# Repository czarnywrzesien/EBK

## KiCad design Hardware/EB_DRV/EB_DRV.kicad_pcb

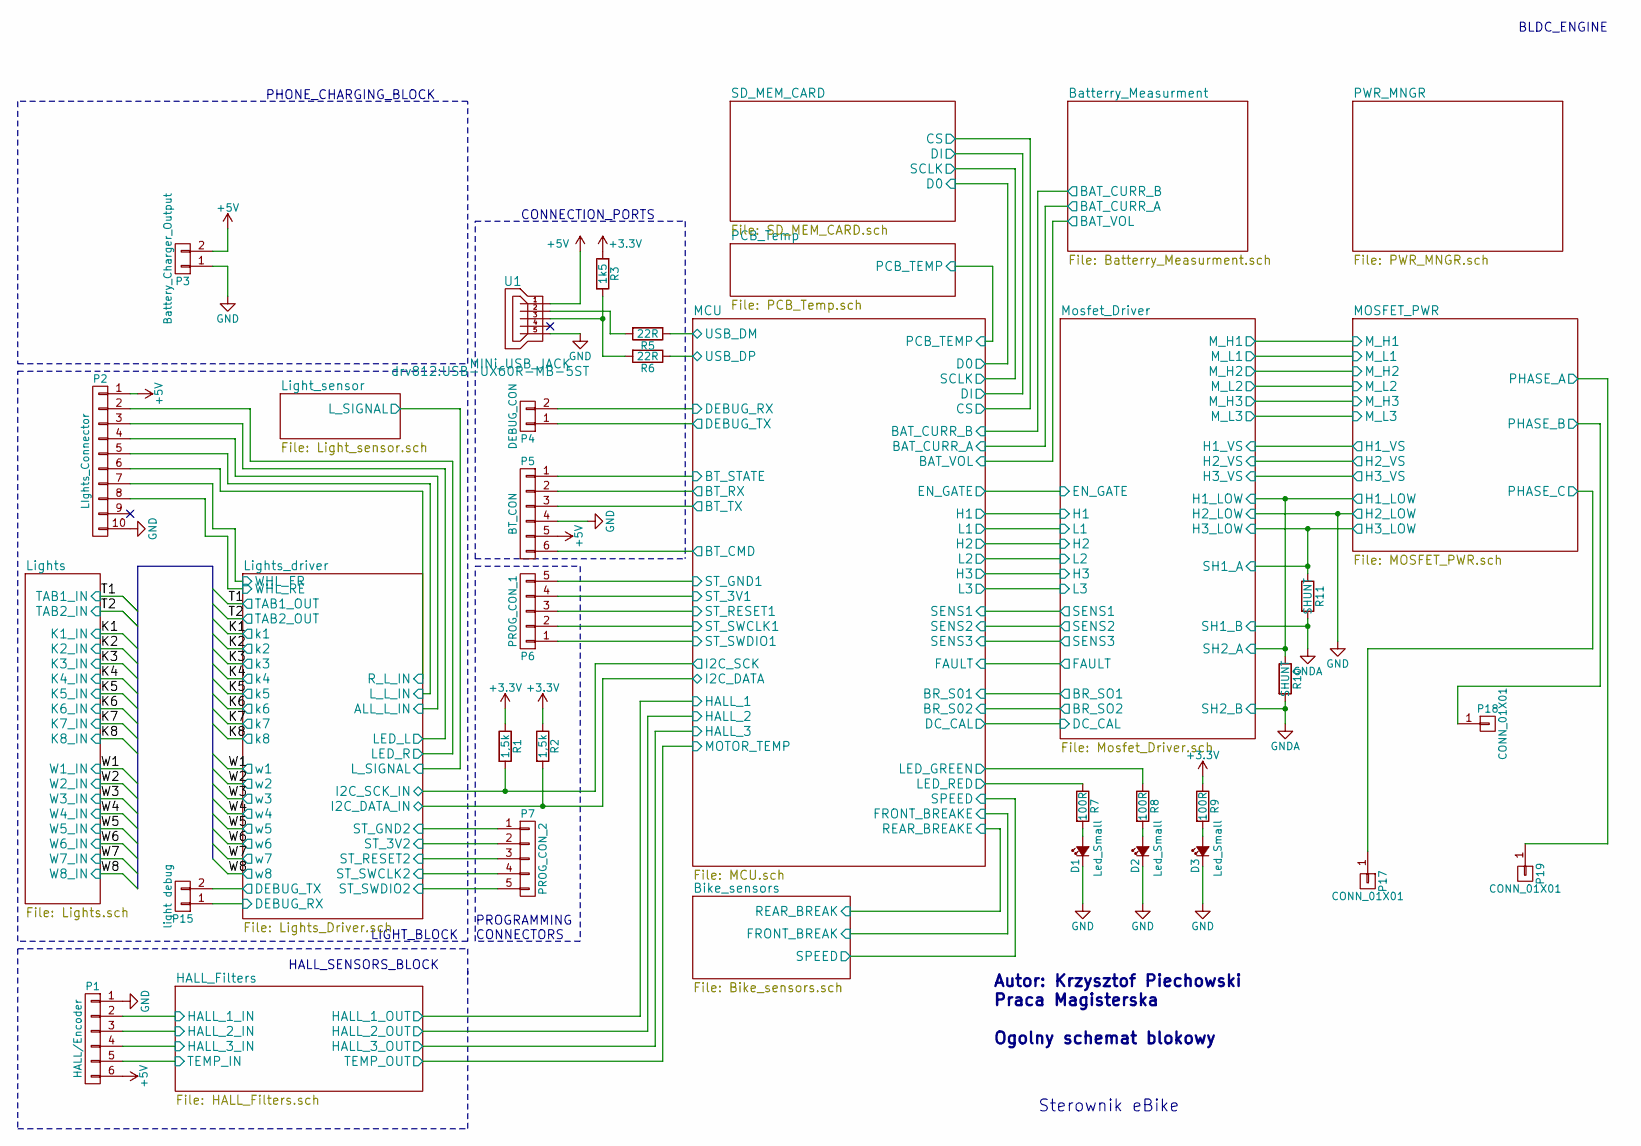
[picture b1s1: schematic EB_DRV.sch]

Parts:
D1, D2, D3: Led_Small; LED_0805
P1: HALL/Encoder; Pin_Header_Straight_1x06
P2: LIghts_Connector; Pin_Header_Straight_1x10
P3: Battery_Charger_Output; Pin_Header_Straight_1x02
P4: DEBUG_CON; Pin_Header_Straight_1x02
P5: BT_CON; Pin_Header_Straight_1x06
P6: PROG_CON_1; Pin_Header_Straight_1x05
P7: PROG_CON_2; Pin_Header_Straight_1x05
P15: light debug; Pin_Header_Straight_1x02
P17, P18, P19: CONN_01X01; SolderWirePad_single_2-5mmDrill
R1, R2: 1,5k; R_0805_HandSoldering
R3: 1k5; R_0805_HandSoldering
R5, R6: 22R; R_0805_HandSoldering
R7, R8, R9: 100R; R_0805_HandSoldering
R10, R11: SHUNT; R_0805_HandSoldering
U1: MINi_USB_JACK; USB-UX60R-MB-5ST

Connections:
+5V: P1.6, P2.1, P3.2, P5.5, U1.1; also elsewhere on the board
/HALL_Filters/HALL_1_IN: P1.2; also elsewhere on the board
/HALL_Filters/HALL_2_IN: P1.3; also elsewhere on the board
/HALL_Filters/HALL_3_IN: P1.4; also elsewhere on the board
/Lights_driver/ALL_L_IN: P2.4; also elsewhere on the board
/Lights_driver/DEBUG_RX: P15.1; also elsewhere on the board
/Lights_driver/DEBUG_TX: P15.2; also elsewhere on the board
/Lights_driver/LED_L: P2.3; also elsewhere on the board
/Lights_driver/LED_R: P2.2; also elsewhere on the board
/Lights_driver/L_L_IN: P2.5; also elsewhere on the board
/Lights_driver/R_L_IN: P2.6; also elsewhere on the board
/Lights_driver/ST_RESET2: P7.3; also elsewhere on the board
/Lights_driver/ST_SWCLK2: P7.4; also elsewhere on the board
/Lights_driver/ST_SWDIO2: P7.5; also elsewhere on the board
/Lights_driver/WHL_FR: P2.7; also elsewhere on the board
/Lights_driver/WHL_RE: P2.8; also elsewhere on the board
/MCU/BT_CMD: P5.6; also elsewhere on the board
/MCU/BT_RX: P5.2; also elsewhere on the board
/MCU/BT_STATE: P5.1; also elsewhere on the board
/MCU/BT_TX: P5.3; also elsewhere on the board
/MCU/DEBUG_RX: P4.2; also elsewhere on the board
/MCU/DEBUG_TX: P4.1; also elsewhere on the board
/MCU/I2C_DATA: R2.2; also elsewhere on the board
/MCU/I2C_SCK: R1.2; also elsewhere on the board
/MCU/LED_GREEN: R8.1; also elsewhere on the board
/MCU/LED_RED: R7.1; also elsewhere on the board
/MCU/MOTOR_TEMP: P1.5; also elsewhere on the board
/MCU/ST_RESET1: P6.3; also elsewhere on the board
/MCU/ST_SWCLK1: P6.2; also elsewhere on the board
/MCU/ST_SWDIO1: P6.1; also elsewhere on the board
/MCU/USB_DM: R5.1; also elsewhere on the board
/MCU/USB_DP: R6.1; also elsewhere on the board
/MOSFET_PWR/H1_LOW: R10.1; also elsewhere on the board
/MOSFET_PWR/H1_VS: P19.1; also elsewhere on the board
/MOSFET_PWR/H2_VS: P18.1; also elsewhere on the board
/MOSFET_PWR/H3_LOW: R11.1; also elsewhere on the board
/MOSFET_PWR/H3_VS: P17.1; also elsewhere on the board
GNDA: R10.2, R11.2; also elsewhere on the board
unnamed: D1.2 (A), R7.2
unnamed: D2.2 (A), R8.2
unnamed: D3.2 (A), R9.2
unnamed: R3.2, R6.2, U1.3
unnamed: R5.2, U1.2

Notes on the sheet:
LIGHT_BLOCK
PHONE_CHARGING_BLOCK
BLDC_ENGINE
HALL_SENSORS_BLOCK
PROGRAMMING CONNECTORS
CONNECTION_PORTS
Autor: Krzysztof Piechowski Praca Magisterska Ogolny schemat blokowy
Sterownik eBike

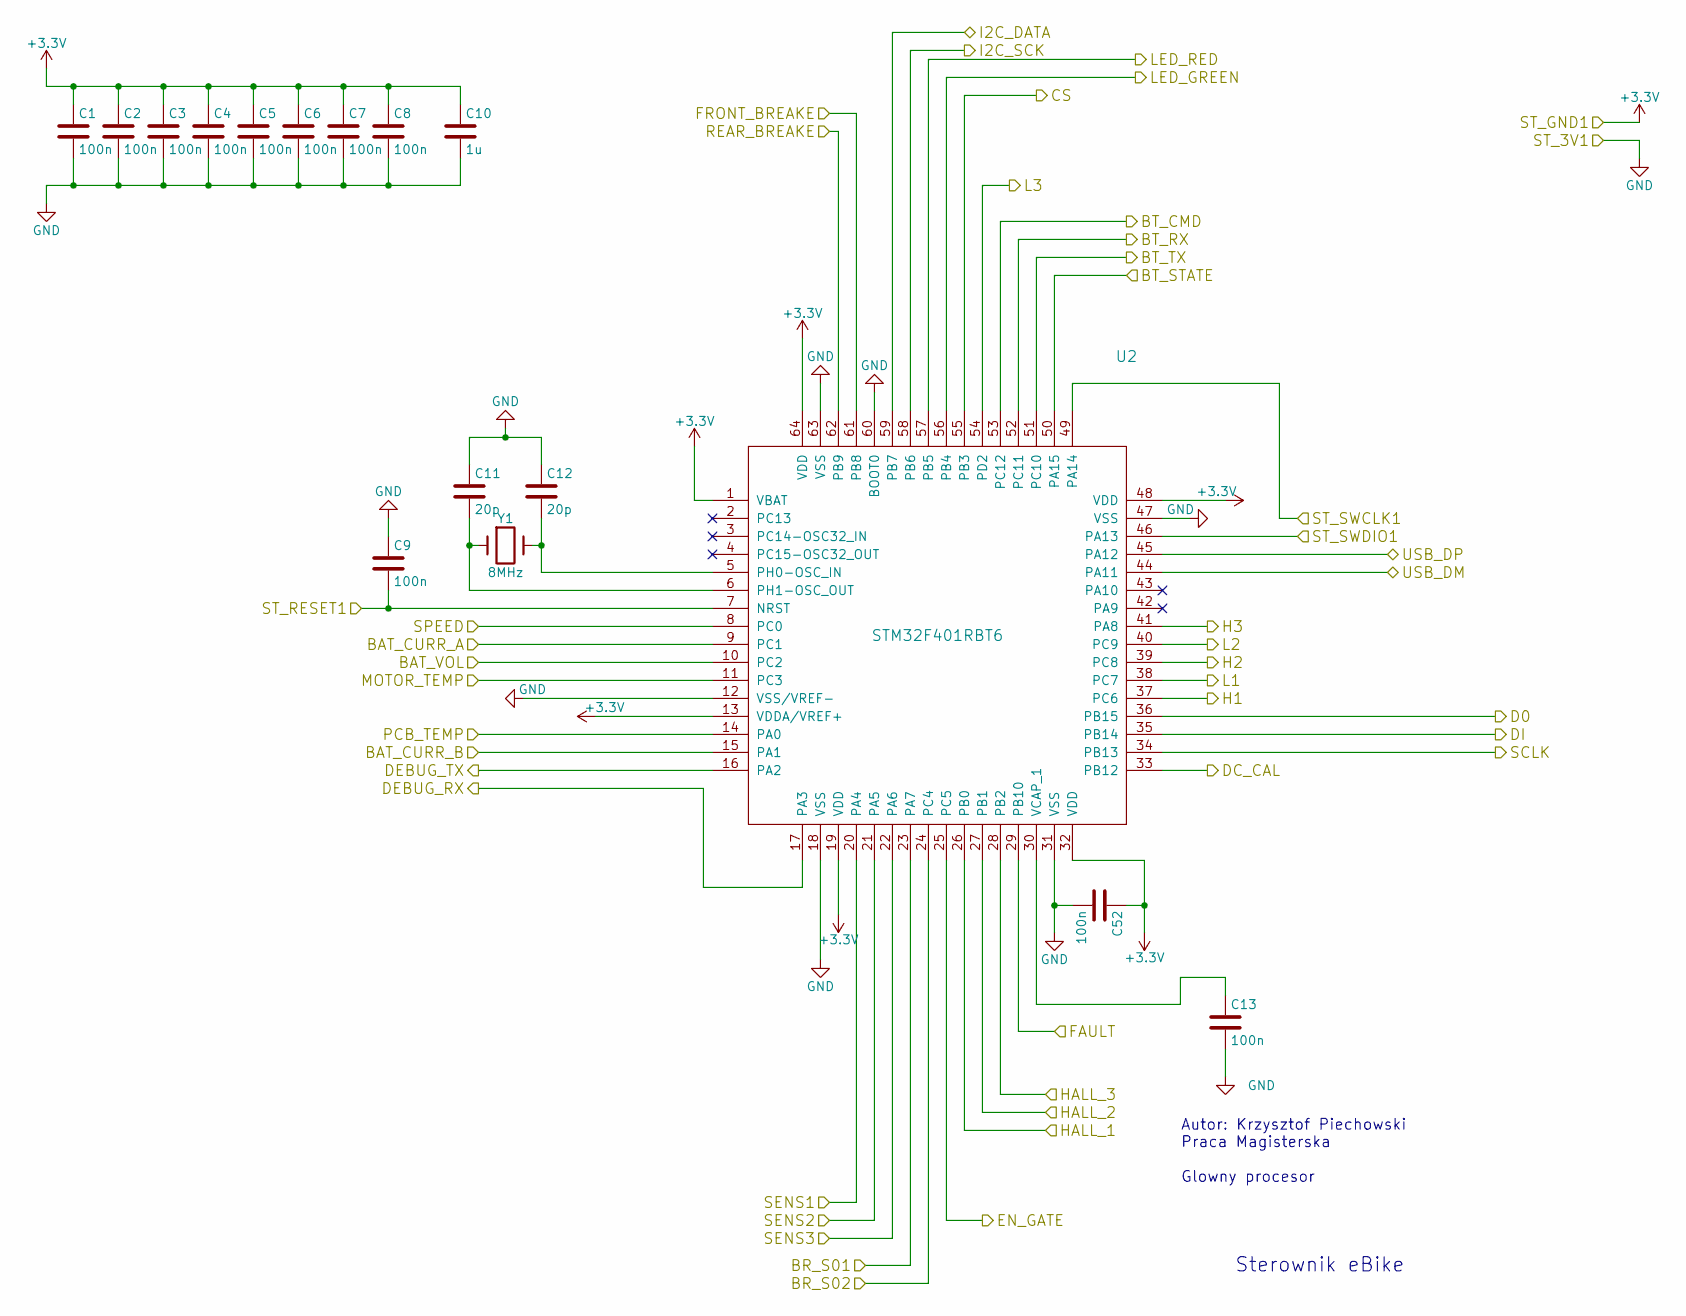
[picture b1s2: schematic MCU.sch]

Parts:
C1, C2, C3, C4, C5, C6, C7, C8, C9, C13, C52: 100n; C_0805_HandSoldering
C10: 1u; C_0805_HandSoldering
C11, C12: 20p; C_0805_HandSoldering
U2: STM32F401RBT6; LQFP-64_10x10mm_Pitch0.5mm
Y1: 8MHz; HC-18UV

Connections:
/Batterry_Measurment/BAT_CURR_A: U2.9 (PC1); also elsewhere on the board
/Batterry_Measurment/BAT_CURR_B: U2.15 (PA1); also elsewhere on the board
/Batterry_Measurment/BAT_VOL: U2.10 (PC2); also elsewhere on the board
/Bike_sensors/FRONT_BREAK: U2.61 (PB8); also elsewhere on the board
/Bike_sensors/REAR_BREAK: U2.62 (PB9); also elsewhere on the board
/Bike_sensors/SPEED: U2.8 (PC0); also elsewhere on the board
/MCU/BR_S01: U2.23 (PA7); also elsewhere on the board
/MCU/BR_S02: U2.24 (PC4); also elsewhere on the board
/MCU/BT_CMD: U2.53 (PC12); also elsewhere on the board
/MCU/BT_RX: U2.52 (PC11); also elsewhere on the board
/MCU/BT_STATE: U2.50 (PA15); also elsewhere on the board
/MCU/BT_TX: U2.51 (PC10); also elsewhere on the board
/MCU/CS: U2.55 (PB3)
/MCU/D0: U2.36 (PB15)
/MCU/DC_CAL: U2.33 (PB12); also elsewhere on the board
/MCU/DEBUG_RX: U2.17 (PA3); also elsewhere on the board
/MCU/DEBUG_TX: U2.16 (PA2); also elsewhere on the board
/MCU/DI: U2.35 (PB14)
/MCU/EN_GATE: U2.25 (PC5); also elsewhere on the board
/MCU/FAULT: U2.29 (PB10); also elsewhere on the board
/MCU/H1: U2.37 (PC6); also elsewhere on the board
/MCU/H2: U2.39 (PC8); also elsewhere on the board
/MCU/H3: U2.41 (PA8); also elsewhere on the board
/MCU/HALL_1: U2.26 (PB0); also elsewhere on the board
/MCU/HALL_2: U2.27 (PB1); also elsewhere on the board
/MCU/HALL_3: U2.28 (PB2); also elsewhere on the board
/MCU/I2C_DATA: U2.59 (PB7); also elsewhere on the board
/MCU/I2C_SCK: U2.58 (PB6); also elsewhere on the board
/MCU/L1: U2.38 (PC7); also elsewhere on the board
/MCU/L2: U2.40 (PC9); also elsewhere on the board
/MCU/L3: U2.54 (PD2); also elsewhere on the board
/MCU/LED_GREEN: U2.56 (PB4); also elsewhere on the board
/MCU/LED_RED: U2.57 (PB5); also elsewhere on the board
/MCU/MOTOR_TEMP: U2.11 (PC3); also elsewhere on the board
/MCU/PCB_TEMP: U2.14 (PA0); also elsewhere on the board
/MCU/SCLK: U2.34 (PB13)
/MCU/SENS1: U2.20 (PA4); also elsewhere on the board
/MCU/SENS2: U2.21 (PA5); also elsewhere on the board
/MCU/SENS3: U2.22 (PA6); also elsewhere on the board
/MCU/ST_RESET1: C9.2, U2.7 (NRST); also elsewhere on the board
/MCU/ST_SWCLK1: U2.49 (PA14); also elsewhere on the board
/MCU/ST_SWDIO1: U2.46 (PA13); also elsewhere on the board
/MCU/USB_DM: U2.44 (PA11); also elsewhere on the board
/MCU/USB_DP: U2.45 (PA12); also elsewhere on the board
unnamed: C11.2, U2.6 (PH1-OSC_OUT), Y1.1
unnamed: C12.2, U2.5 (PH0-OSC_IN), Y1.2
unnamed: C13.1, U2.30 (VCAP_1)

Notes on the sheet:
Autor: Krzysztof Piechowski Praca Magisterska Glowny procesor
Sterownik eBike

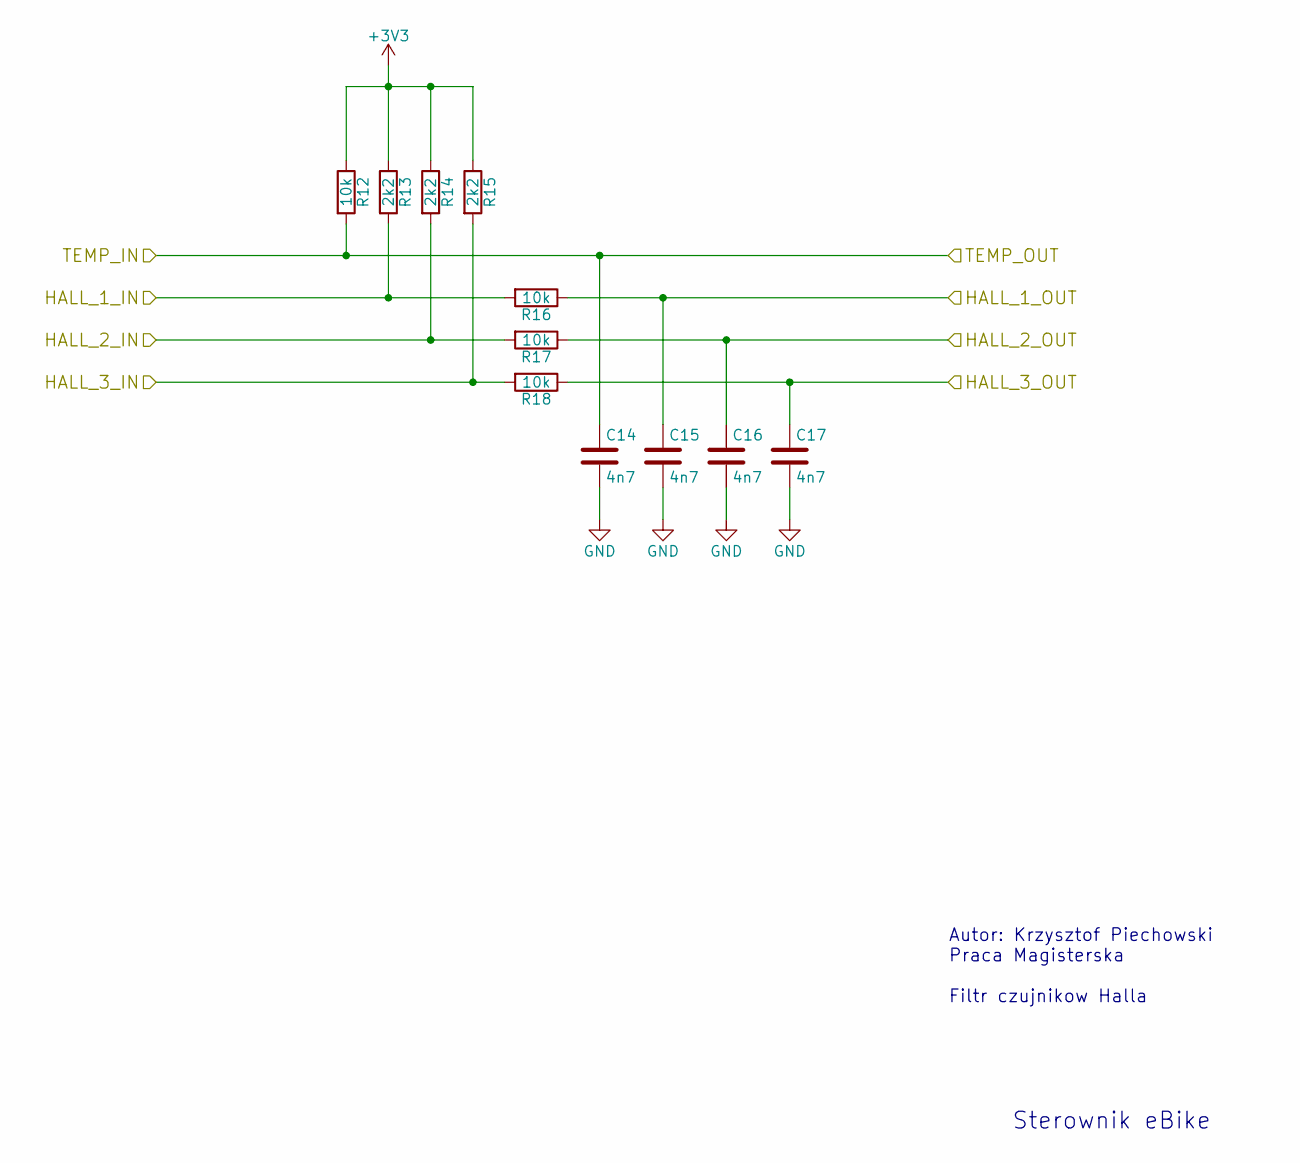
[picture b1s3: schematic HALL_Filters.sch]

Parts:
C14, C15, C16, C17: 4n7; C_0805_HandSoldering
R12, R16, R17, R18: 10k; R_0805_HandSoldering
R13, R14, R15: 2k2; R_0805_HandSoldering

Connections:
/HALL_Filters/HALL_1_IN: R13.2, R16.2; also elsewhere on the board
/HALL_Filters/HALL_2_IN: R14.2, R17.2; also elsewhere on the board
/HALL_Filters/HALL_3_IN: R15.2, R18.2; also elsewhere on the board
/MCU/HALL_1: C15.1, R16.1; also elsewhere on the board
/MCU/HALL_2: C16.1, R17.1; also elsewhere on the board
/MCU/HALL_3: C17.1, R18.1; also elsewhere on the board
/MCU/MOTOR_TEMP: C14.1, R12.2; also elsewhere on the board

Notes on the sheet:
Autor: Krzysztof Piechowski Praca Magisterska Filtr czujnikow Halla
Sterownik eBike

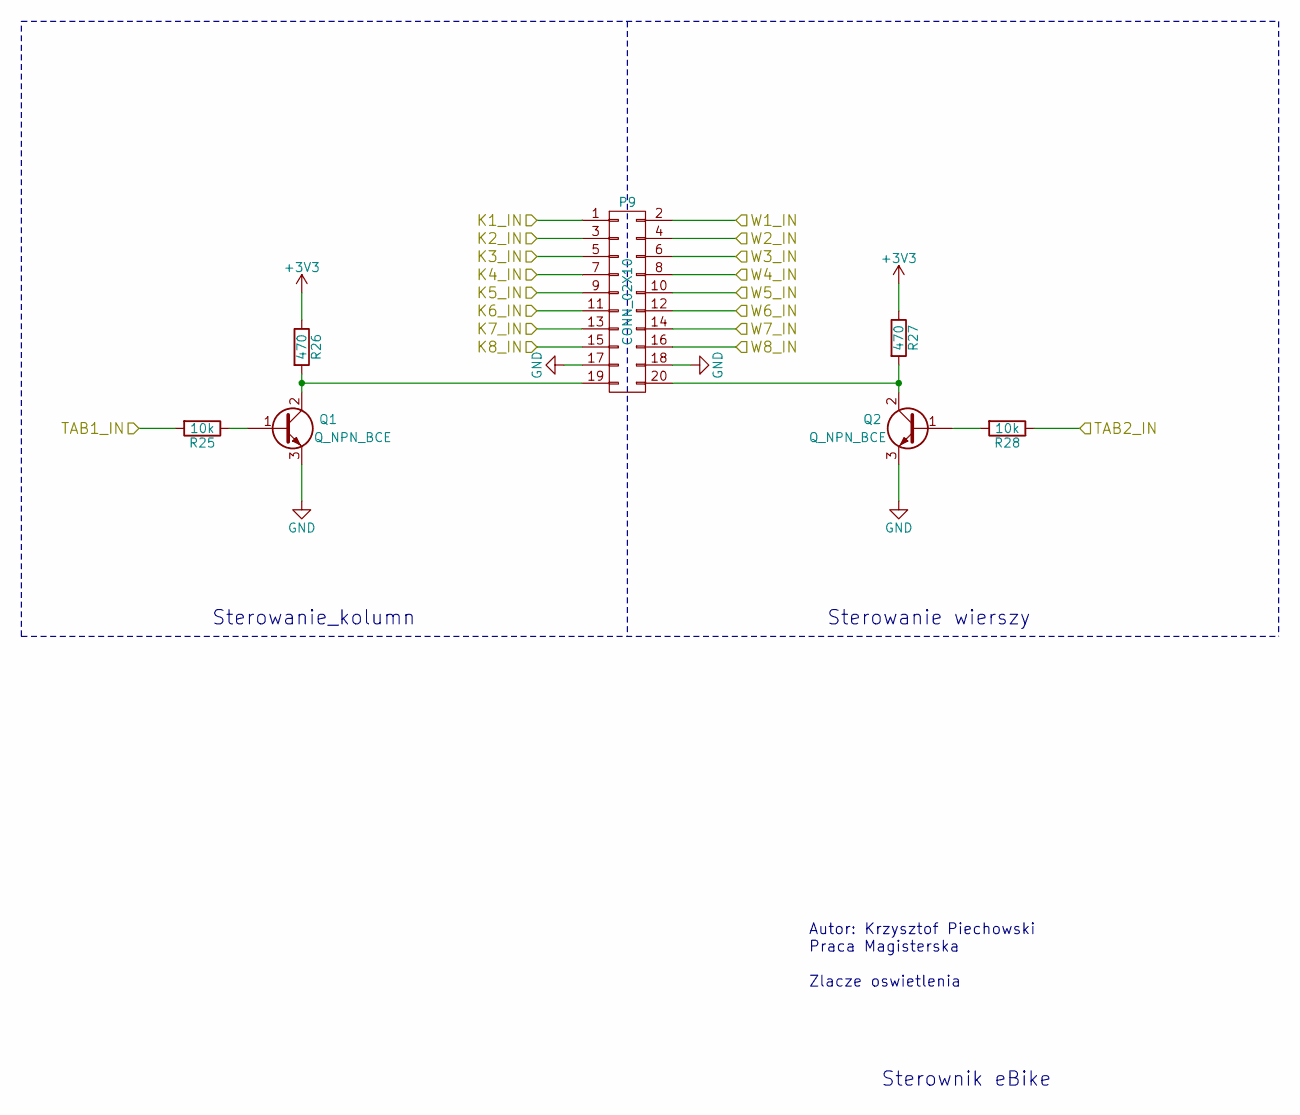
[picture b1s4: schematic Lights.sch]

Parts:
P9: CONN_02X10; Pin_Header_Straight_2x10
Q1, Q2: Q_NPN_BCE; SOT-323
R25, R28: 10k; R_0805_HandSoldering
R26, R27: 470; R_0805_HandSoldering

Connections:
/Lights/K1_IN: P9.1; also elsewhere on the board
/Lights/K2_IN: P9.3; also elsewhere on the board
/Lights/K3_IN: P9.5; also elsewhere on the board
/Lights/K4_IN: P9.7; also elsewhere on the board
/Lights/K5_IN: P9.9; also elsewhere on the board
/Lights/K6_IN: P9.11; also elsewhere on the board
/Lights/K7_IN: P9.13; also elsewhere on the board
/Lights/K8_IN: P9.15; also elsewhere on the board
/Lights/TAB1_IN: R25.2; also elsewhere on the board
/Lights/TAB2_IN: R28.1; also elsewhere on the board
/Lights/W1_IN: P9.2; also elsewhere on the board
/Lights/W2_IN: P9.4; also elsewhere on the board
/Lights/W3_IN: P9.6; also elsewhere on the board
/Lights/W4_IN: P9.8; also elsewhere on the board
/Lights/W5_IN: P9.10; also elsewhere on the board
/Lights/W6_IN: P9.12; also elsewhere on the board
/Lights/W7_IN: P9.14; also elsewhere on the board
/Lights/W8_IN: P9.16; also elsewhere on the board
unnamed: P9.19, Q1.2 (C), R26.2
unnamed: P9.20, Q2.2 (C), R27.2
unnamed: Q1.1 (B), R25.1
unnamed: Q2.1 (B), R28.2

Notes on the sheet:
Autor: Krzysztof Piechowski Praca Magisterska Zlacze oswietlenia
Sterowanie_kolumn
Sterowanie wierszy
Sterownik eBike

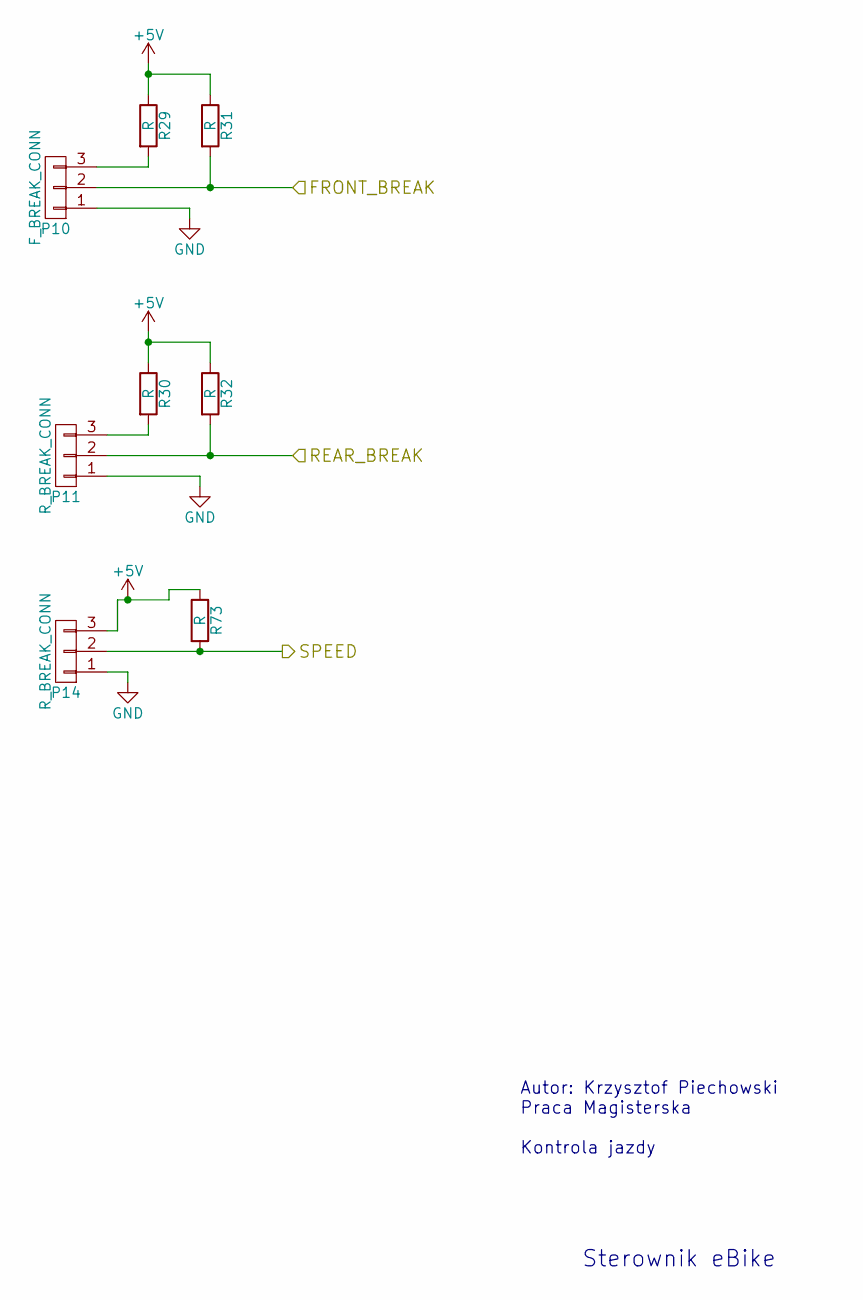
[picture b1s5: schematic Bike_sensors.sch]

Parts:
P10: F_BREAK_CONN; Pin_Header_Straight_1x03
P11, P14: R_BREAK_CONN; Pin_Header_Straight_1x03
R29, R30, R31, R32, R73: R; R_0805_HandSoldering

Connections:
+5V: P14.3, R29.1, R30.1, R31.1, R32.1, R73.1; also elsewhere on the board
/Bike_sensors/FRONT_BREAK: P10.2, R31.2; also elsewhere on the board
/Bike_sensors/REAR_BREAK: P11.2, R32.2; also elsewhere on the board
/Bike_sensors/SPEED: P14.2, R73.2; also elsewhere on the board
unnamed: P10.3, R29.2
unnamed: P11.3, R30.2

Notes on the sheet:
Autor: Krzysztof Piechowski Praca Magisterska Kontrola jazdy
Sterownik eBike

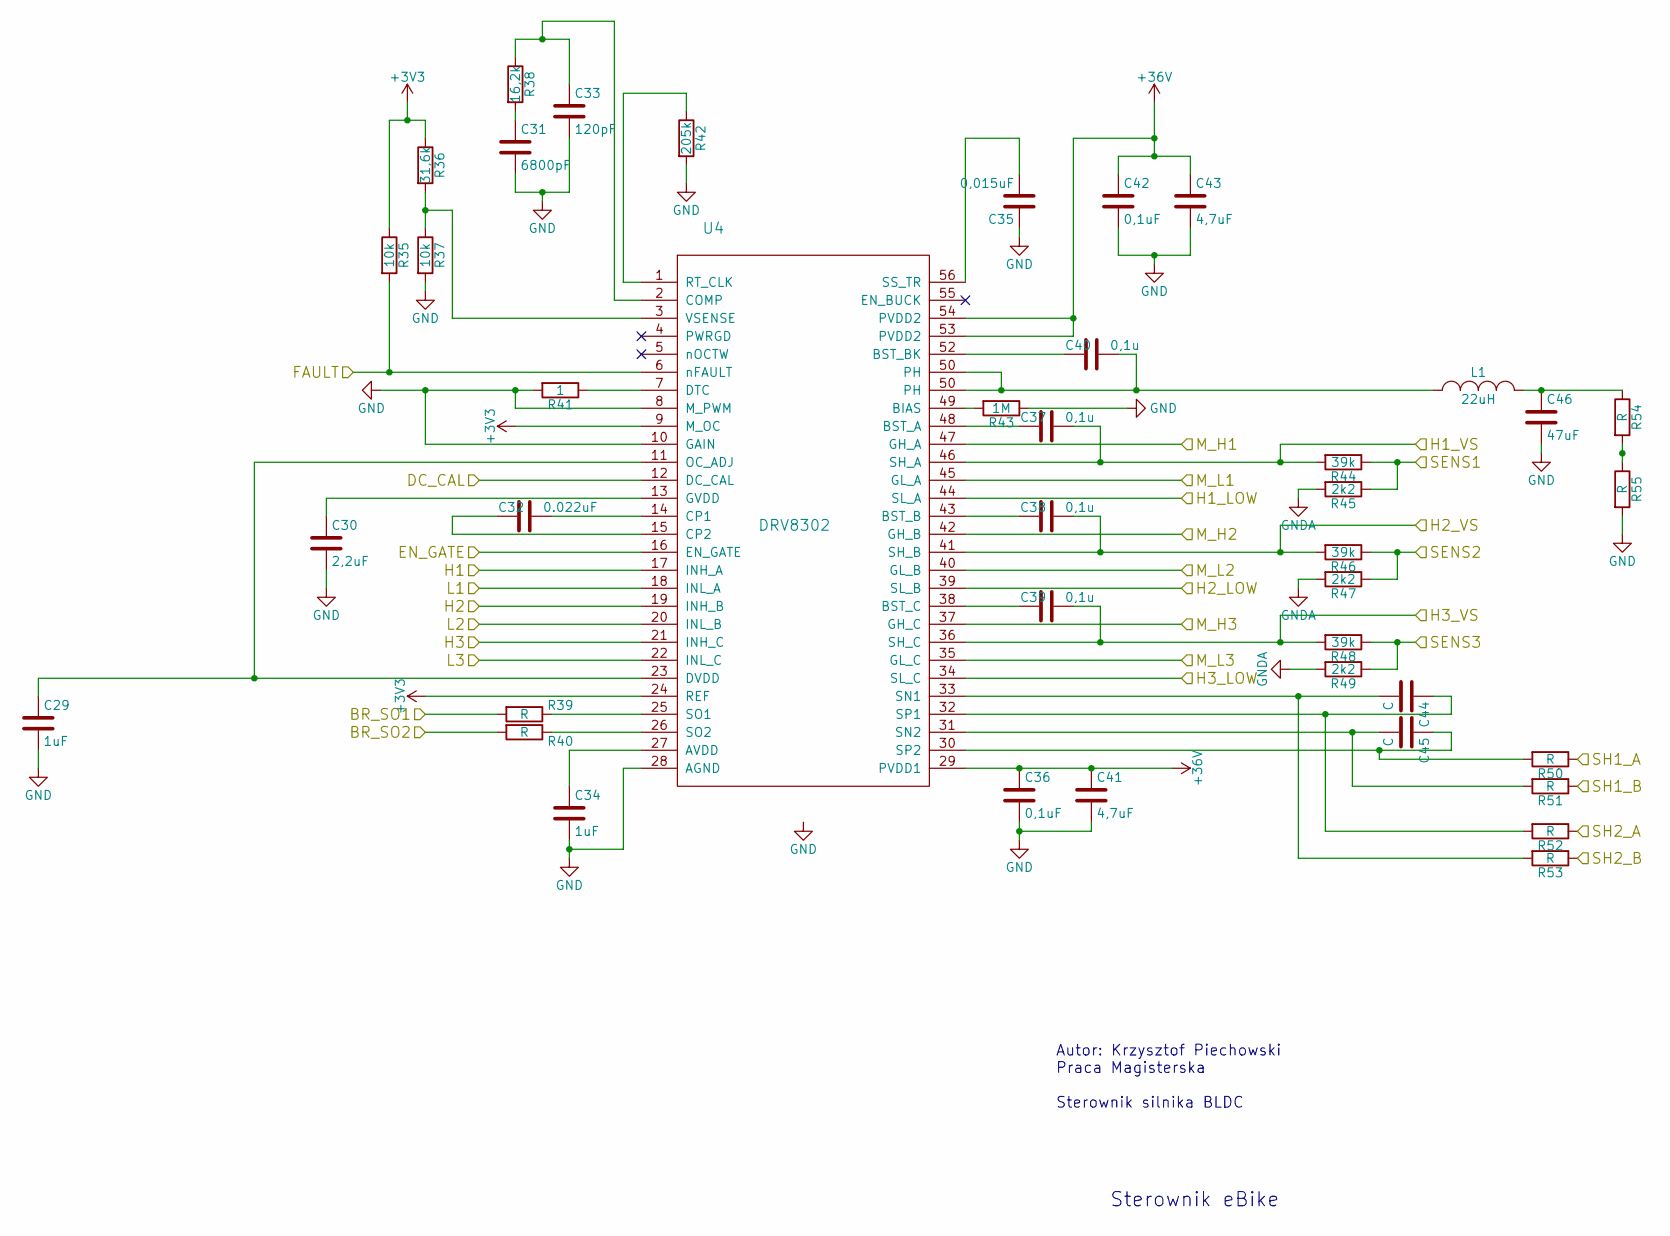
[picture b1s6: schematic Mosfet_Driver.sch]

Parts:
C29, C34: 1uF; C_0805_HandSoldering
C30: 2,2uF; C_0805_HandSoldering
C31: 6800pF; C_0805_HandSoldering
C32: 0.022uF; C_0805_HandSoldering
C33: 120pF; C_0805_HandSoldering
C35: 0,015uF; C_0805_HandSoldering
C36, C42: 0,1uF; C_0805_HandSoldering
C37, C38, C39, C40: 0,1u; C_0805_HandSoldering
C41, C43: 4,7uF; C_0805_HandSoldering
C44, C45: C; C_0805_HandSoldering
C46: 47uF; C_0805_HandSoldering
L1: 22uH; NR4018_HandSoldering
R35, R37: 10k; R_0805_HandSoldering
R36: 31,6k; R_0805_HandSoldering
R38: 16,2k; R_0805_HandSoldering
R39, R40, R50, R51, R52, R53, R54, R55: R; R_0805_HandSoldering
R41: 1; R_0805_HandSoldering
R42: 205k; R_0805_HandSoldering
R43: 1M; R_0805_HandSoldering
R44, R46, R48: 39k; R_0805_HandSoldering
R45, R47, R49: 2k2; R_0805_HandSoldering
U4: DRV8302; TSSOP-56-PP

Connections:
+36V: C36.1, C41.1, C42.1, C43.1, U4.29 (PVDD1), U4.53 (PVDD2), U4.54 (PVDD2); also elsewhere on the board
/MCU/BR_S01: R39.2; also elsewhere on the board
/MCU/BR_S02: R40.2; also elsewhere on the board
/MCU/DC_CAL: U4.12 (DC_CAL); also elsewhere on the board
/MCU/EN_GATE: U4.16 (EN_GATE); also elsewhere on the board
/MCU/FAULT: R35.2, U4.6 (nFAULT); also elsewhere on the board
/MCU/H1: U4.17 (INH_A); also elsewhere on the board
/MCU/H2: U4.19 (INH_B); also elsewhere on the board
/MCU/H3: U4.21 (INH_C); also elsewhere on the board
/MCU/L1: U4.18 (INL_A); also elsewhere on the board
/MCU/L2: U4.20 (INL_B); also elsewhere on the board
/MCU/L3: U4.22 (INL_C); also elsewhere on the board
/MCU/SENS1: R44.1, R45.1; also elsewhere on the board
/MCU/SENS2: R46.1, R47.1; also elsewhere on the board
/MCU/SENS3: R48.1, R49.1; also elsewhere on the board
/MOSFET_PWR/H1_LOW: R52.1, U4.44 (SL_A); also elsewhere on the board
/MOSFET_PWR/H1_VS: C37.1, R44.2, U4.46 (SH_A); also elsewhere on the board
/MOSFET_PWR/H2_VS: C38.1, R46.2, U4.41 (SH_B); also elsewhere on the board
/MOSFET_PWR/H3_LOW: R50.1, U4.34 (SL_C); also elsewhere on the board
/MOSFET_PWR/H3_VS: C39.1, R48.2, U4.36 (SH_C); also elsewhere on the board
/MOSFET_PWR/M_H1: U4.47 (GH_A); also elsewhere on the board
/MOSFET_PWR/M_H2: U4.42 (GH_B); also elsewhere on the board
/MOSFET_PWR/M_H3: U4.37 (GH_C); also elsewhere on the board
/MOSFET_PWR/M_L1: U4.45 (GL_A); also elsewhere on the board
/MOSFET_PWR/M_L2: U4.40 (GL_B); also elsewhere on the board
/MOSFET_PWR/M_L3: U4.35 (GL_C); also elsewhere on the board
GNDA: R45.2, R47.2, R49.2, R51.1, R53.1; also elsewhere on the board
unnamed: C29.1, U4.11 (OC_ADJ), U4.23 (DVDD)
unnamed: C30.1, U4.13 (GVDD)
unnamed: C31.1, R38.2
unnamed: C32.1, U4.14 (CP1)
unnamed: C32.2, U4.15 (CP2)
unnamed: C33.1, R38.1, U4.2 (COMP)
unnamed: C34.1, U4.27 (AVDD)
unnamed: C35.2, U4.56 (SS_TR)
unnamed: C37.2, U4.48 (BST_A)
unnamed: C38.2, U4.43 (BST_B)
unnamed: C39.2, U4.38 (BST_C)
unnamed: C40.1, L1.1, U4.50 (PH)
unnamed: C40.2, U4.52 (BST_BK)
unnamed: C44.1, R52.2, U4.32 (SP1)
unnamed: C44.2, R53.2, U4.33 (SN1)
unnamed: C45.1, R50.2, U4.30 (SP2)
unnamed: C45.2, R51.2, U4.31 (SN2)
unnamed: C46.1, L1.2, R54.1
unnamed: R36.2, R37.1, U4.3 (VSENSE)
unnamed: R39.1, U4.25 (SO1)
unnamed: R40.1, U4.26 (SO2)
unnamed: R41.1, U4.7 (DTC)
unnamed: R42.1, U4.1 (RT_CLK)
unnamed: R43.2, U4.49 (BIAS)
unnamed: R54.2, R55.1

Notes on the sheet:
Autor: Krzysztof Piechowski Praca Magisterska Sterownik silnika BLDC
Sterownik eBike

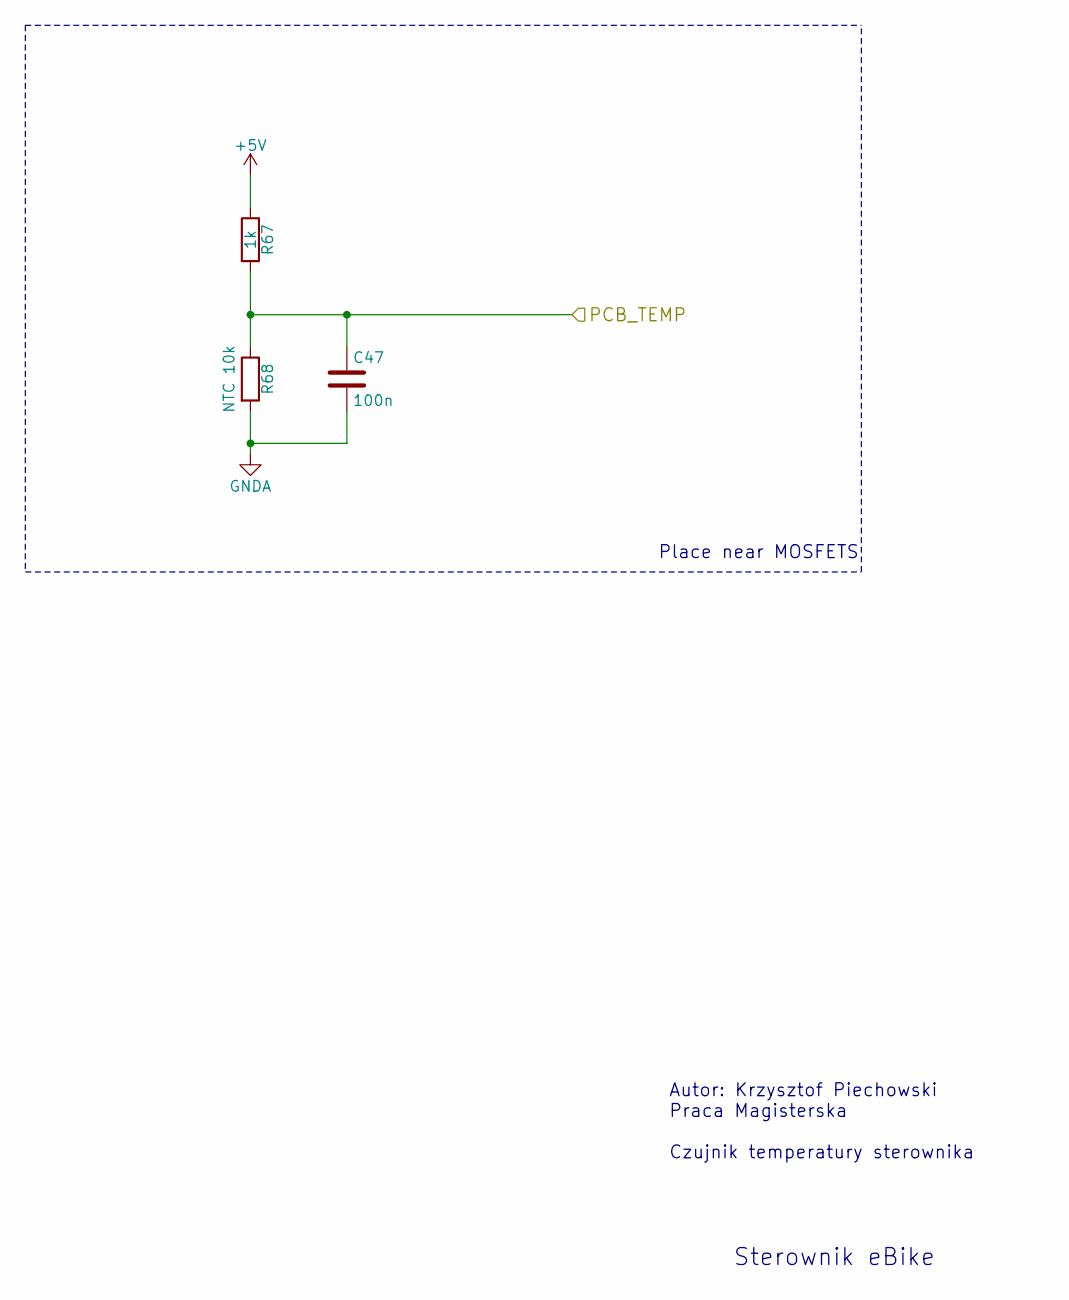
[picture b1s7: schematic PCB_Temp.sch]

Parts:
C47: 100n; C_0805_HandSoldering
R67: 1k; R_0805_HandSoldering
R68: NTC 10k; R_0805_HandSoldering

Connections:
+5V: R67.1; also elsewhere on the board
/MCU/PCB_TEMP: C47.1, R67.2, R68.1; also elsewhere on the board
GNDA: C47.2, R68.2; also elsewhere on the board

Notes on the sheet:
Autor: Krzysztof Piechowski Praca Magisterska Czujnik temperatury sterownika
Place near MOSFETS
Sterownik eBike

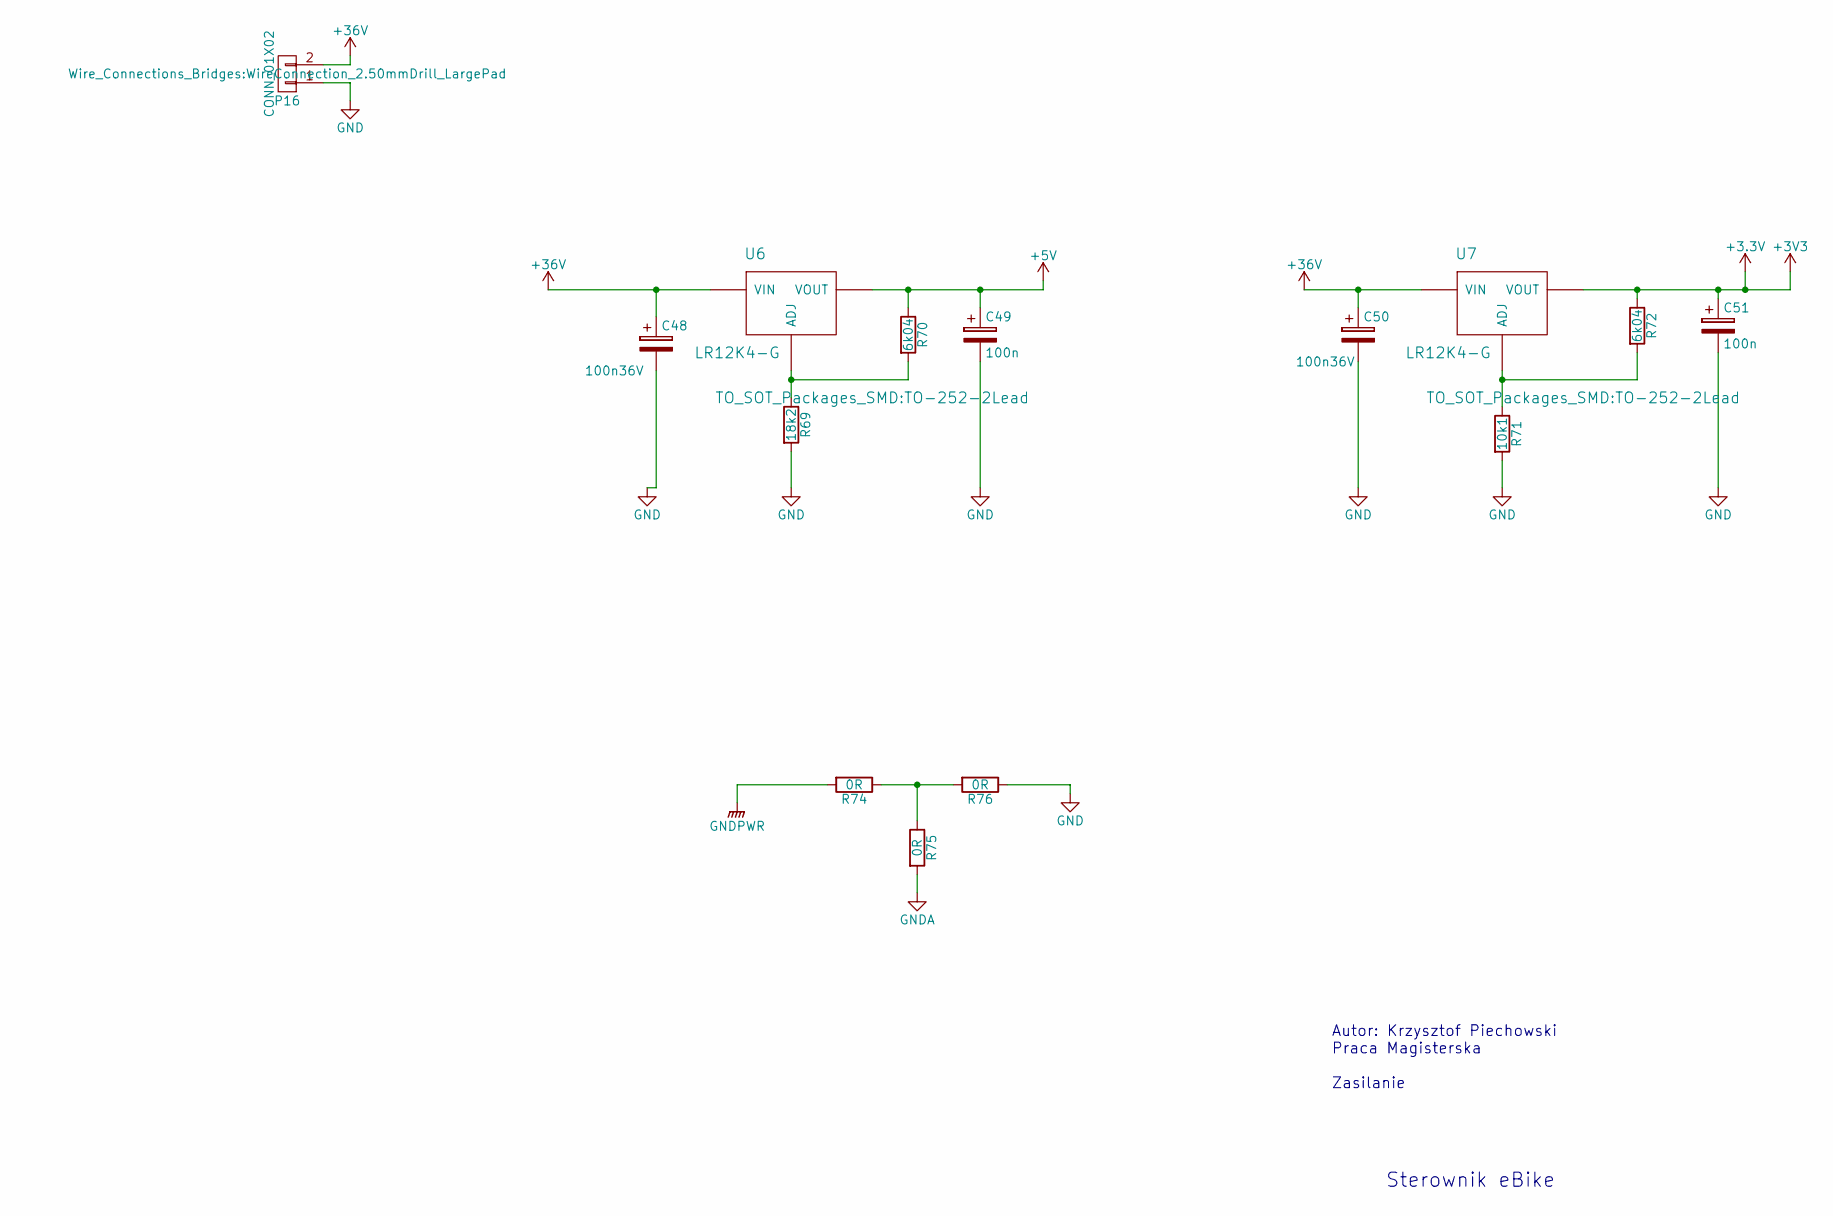
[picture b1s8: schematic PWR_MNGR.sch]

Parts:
C48, C50: 100n36V; C_0805_HandSoldering
C49, C51: 100n; C_0805_HandSoldering
P16: CONN_01X02; WireConnection_2.50mmDrill_LargePad
R69: 18k2; R_0805_HandSoldering
R70, R72: 6k04; R_0805_HandSoldering
R71: 10k1; R_0805_HandSoldering
R74, R75, R76: 0R; R_0805_HandSoldering
U6, U7: LR12K4-G; TO-252-2Lead

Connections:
+5V: C49.1, R70.1, U6.~; also elsewhere on the board
+36V: C48.1, C50.1, P16.2, U6.~, U7.~; also elsewhere on the board
GNDA: R75.2; also elsewhere on the board
GNDPWR: R74.2
unnamed: R69.1, R70.2, U6.~
unnamed: R71.1, R72.2, U7.~
unnamed: R74.1, R75.1, R76.2

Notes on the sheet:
Autor: Krzysztof Piechowski Praca Magisterska Zasilanie
Sterownik eBike
